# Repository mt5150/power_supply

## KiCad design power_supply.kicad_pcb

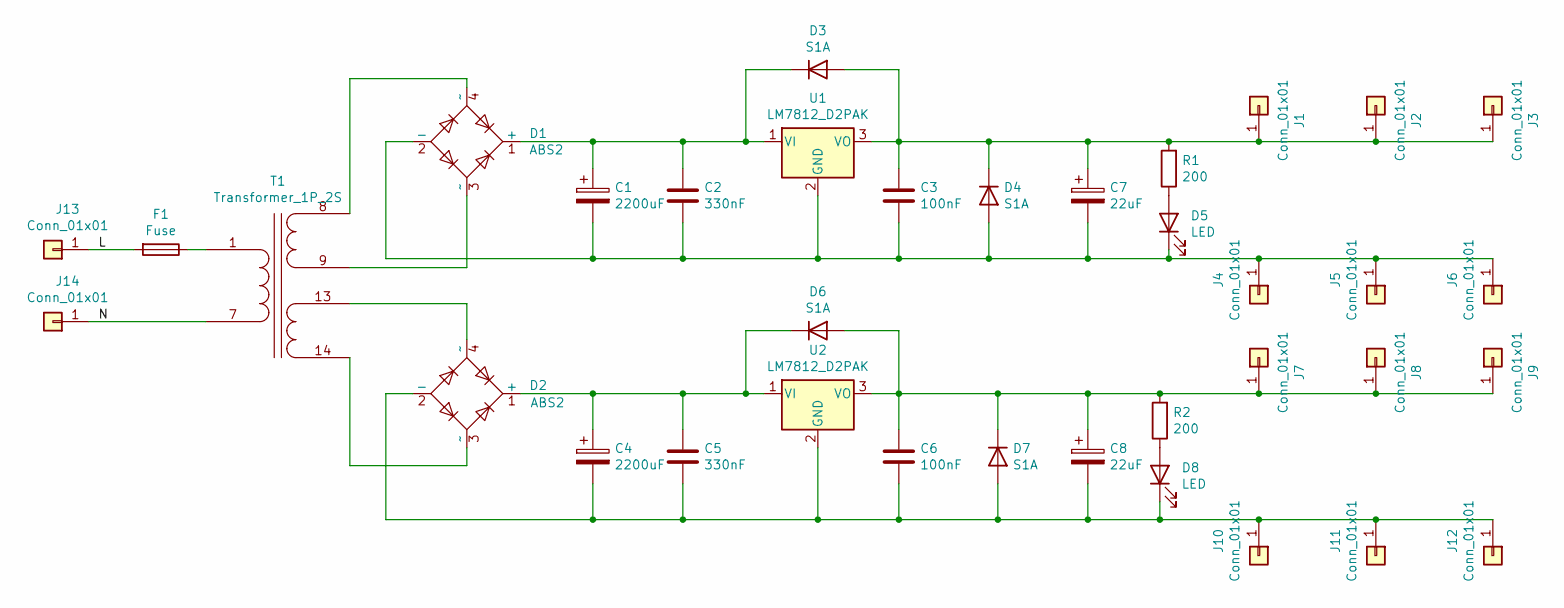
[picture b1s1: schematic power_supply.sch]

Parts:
C1, C4: 2200uF; CP_Radial_D12.5mm_P5.00mm
C2, C5: 330nF; C_0805_2012Metric
C3, C6: 100nF; C_0805_2012Metric
C7, C8: 22uF; CP_EIA-7343-15_Kemet-W
D1, D2: ABS2; Diode_Bridge_Diotec_ABS
D3, D4, D6, D7: S1A; D_SMA
D5, D8: LED; LED_0603_1608Metric
F1: Fuse; Fuse_0603_1608Metric_Castellated
J1, J2, J3, J4, J5, J6, J7, J8, J9, J10, J11, J12, J13, J14: Conn_01x01; TestPoint_THTPad_D1.5mm_Drill0.7mm
R1, R2: 200; R_0603_1608Metric
T1: Transformer_1P_2S; Transformer_TSZZ45_010M_5_INDEL
U1, U2: LM7812_D2PAK; TO-263-2

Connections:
/L: F1.2, J13.1
/N: J14.1, T1.7 (AB)
unnamed: C1.1, C2.1, D1.1 (+), D3.1 (K), U1.1 (VI)
unnamed: C1.2, C2.2, C3.2, C7.2, D1.2 (-), D4.2 (A), D5.1 (K), J4.1, J5.1, J6.1, U1.2 (GND)
unnamed: C3.1, C7.1, D3.2 (A), D4.1 (K), J1.1, J2.1, J3.1, R1.2, U1.3 (VO)
unnamed: C4.1, C5.1, D2.1 (+), D6.1 (K), U2.1 (VI)
unnamed: C4.2, C5.2, C6.2, C8.2, D2.2 (-), D7.2 (A), D8.1 (K), J10.1, J11.1, J12.1, U2.2 (GND)
unnamed: C6.1, C8.1, D6.2 (A), D7.1 (K), J7.1, J8.1, J9.1, R2.2, U2.3 (VO)
unnamed: D1.3 (~~), T1.9 (SB)
unnamed: D1.4 (~~), T1.8 (SA)
unnamed: D2.3 (~~), T1.14 (SD)
unnamed: D2.4 (~~), T1.13 (SC)
unnamed: D5.2 (A), R1.1
unnamed: D8.2 (A), R2.1
unnamed: F1.1, T1.1 (AA)

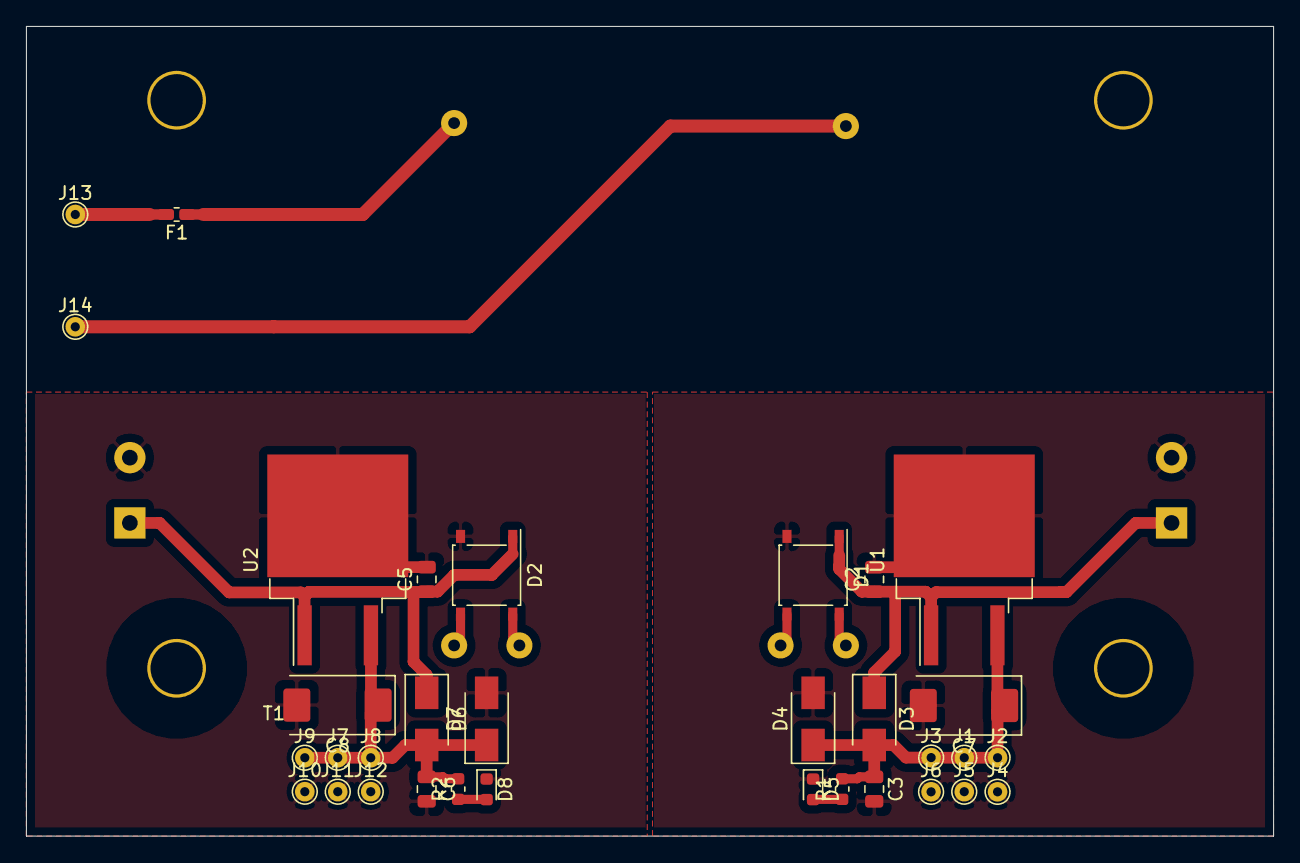
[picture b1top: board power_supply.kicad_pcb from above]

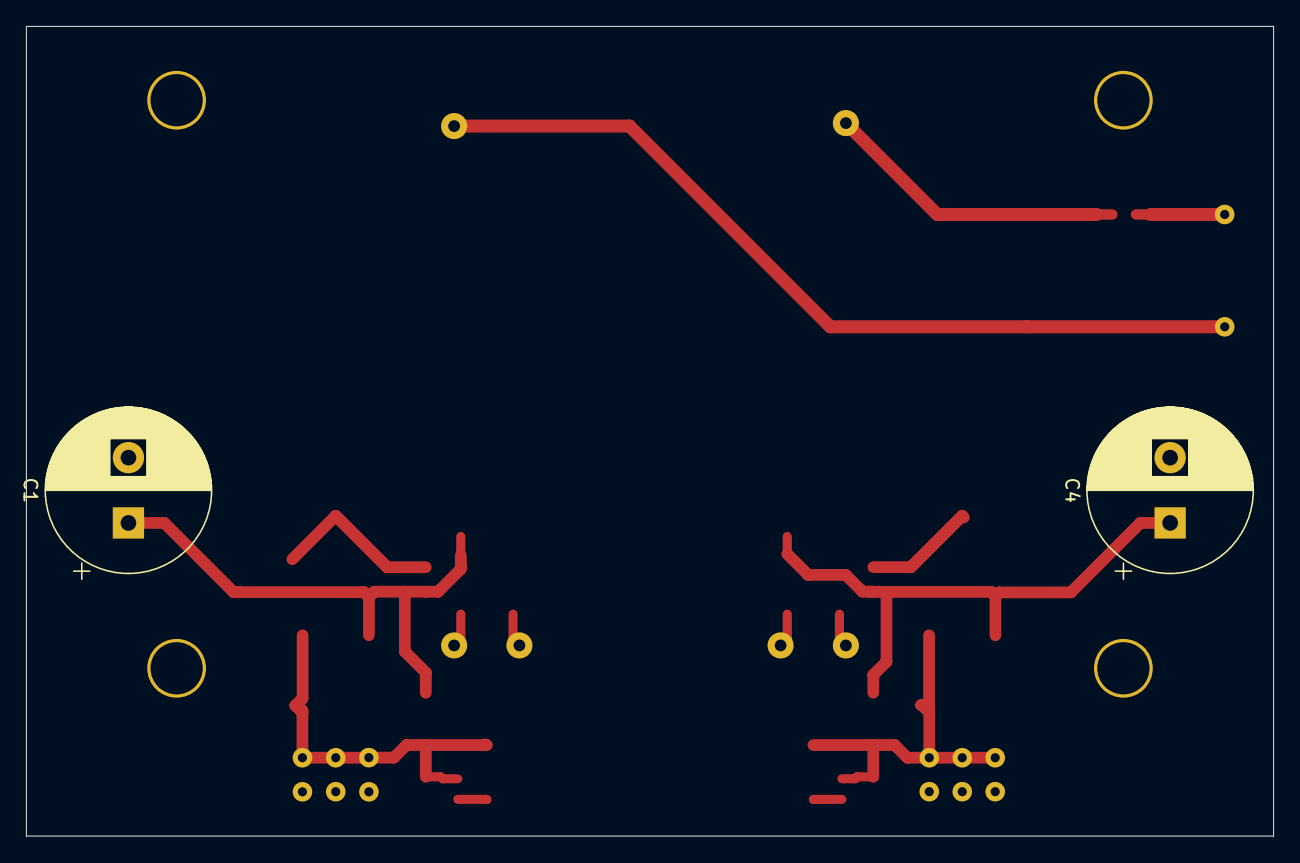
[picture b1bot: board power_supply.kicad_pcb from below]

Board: 2 copper layers, 95.5 x 62.0 mm, 36 parts (2 on the bottom side), 15 nets.

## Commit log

2023-06-19 init
